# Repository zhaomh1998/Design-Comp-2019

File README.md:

# **Team PI/Stroll Easy**
## This repo is dedicated to all the files created for UCSD 2019 Design Competetion

### Participating Parties:
* < Add Names Here >

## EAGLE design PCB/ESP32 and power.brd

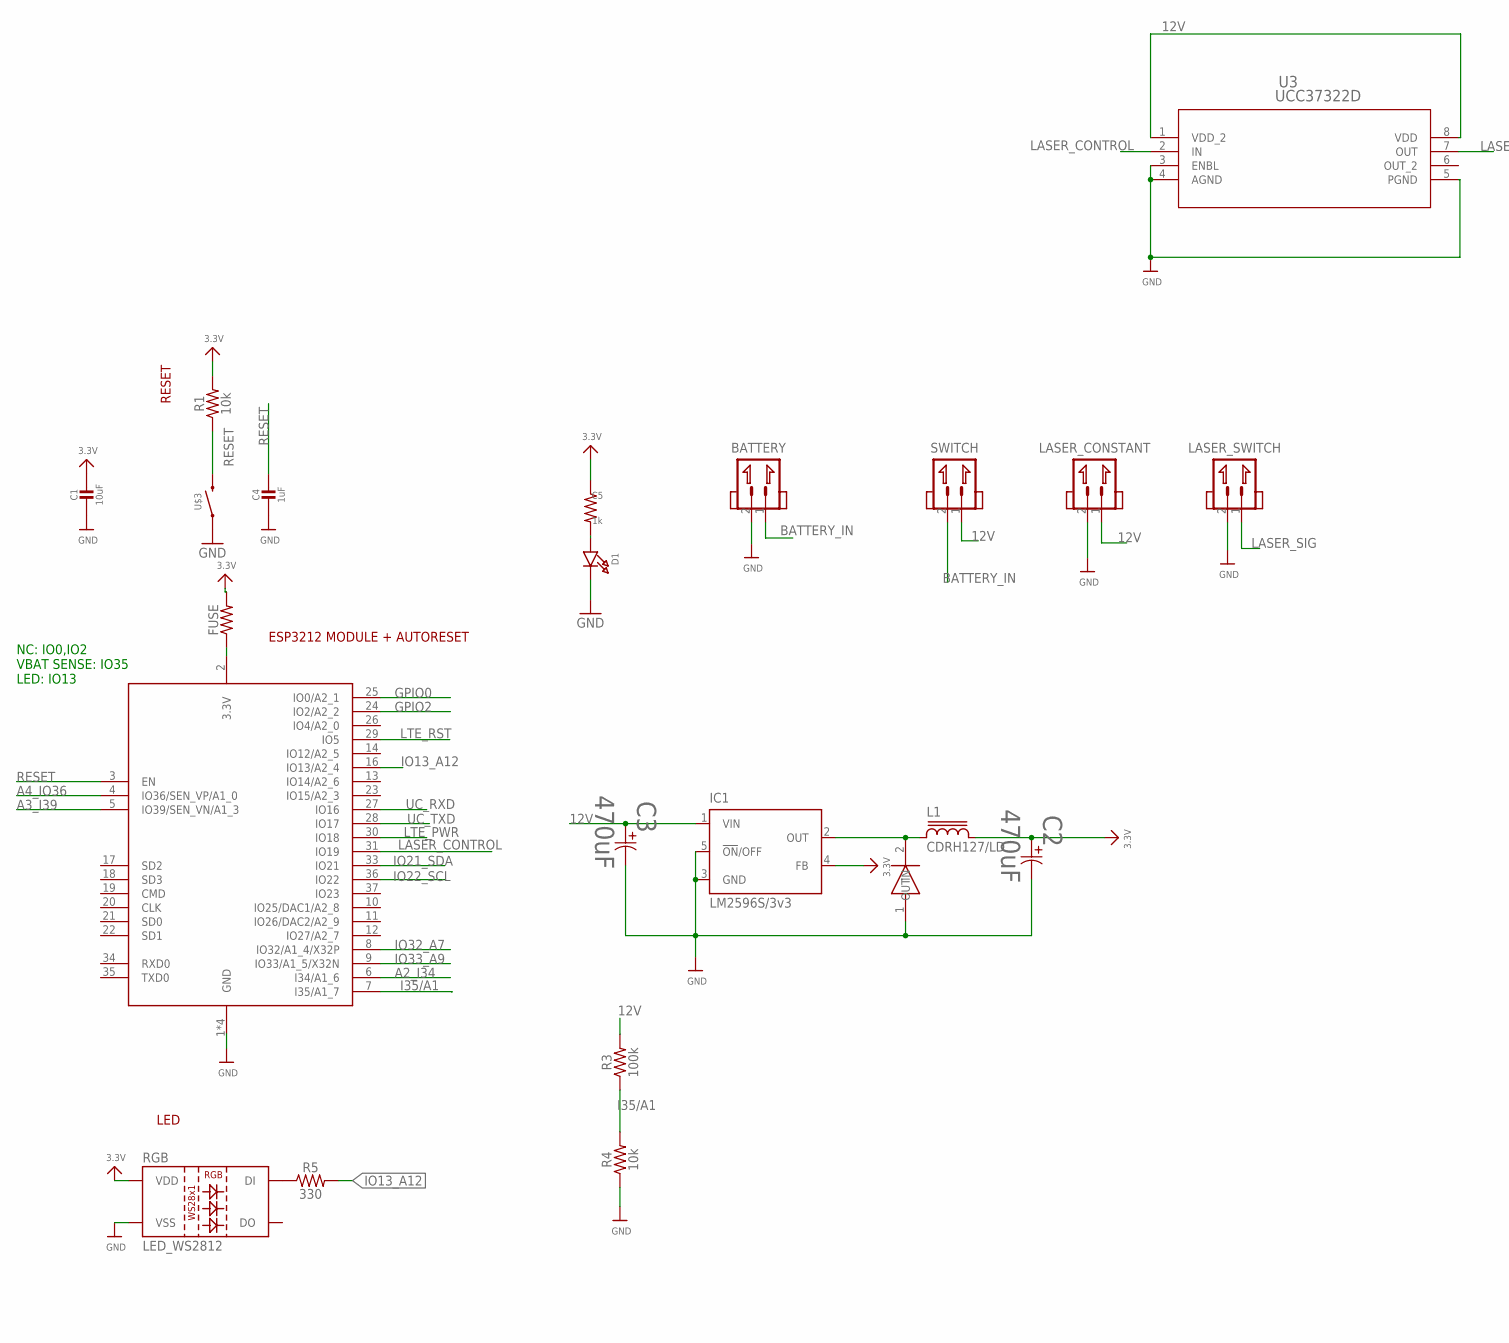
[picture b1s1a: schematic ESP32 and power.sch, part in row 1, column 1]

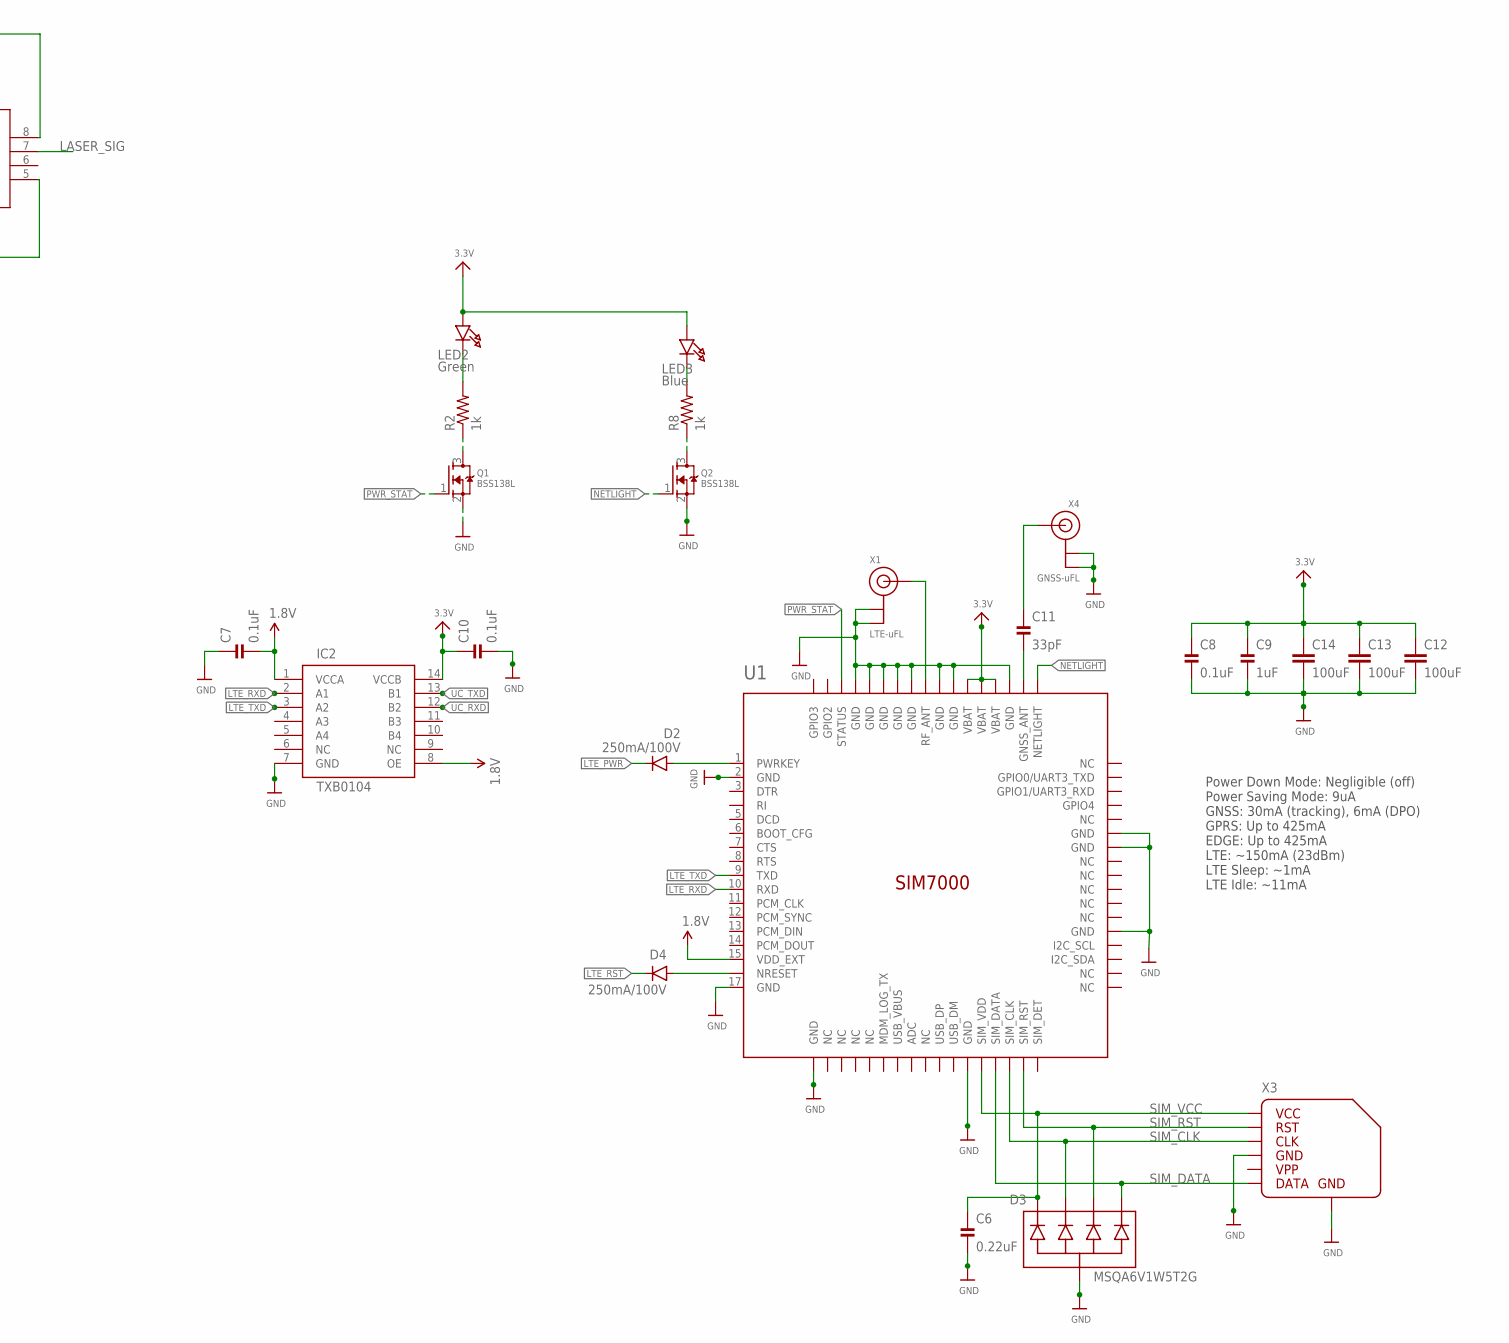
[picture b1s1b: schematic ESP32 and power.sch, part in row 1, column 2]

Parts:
BATTERY: JST_XH_2.54_2P
C1: 10uF; CAP_0603
C2, C3: 470uF; PCAP_8X10-ELECT
C4, C9: 1uF; CAP_0603
C5: 1k; 0603
C6: 0.22uF; CAP_0603
C7, C8, C10: 0.1uF; CAP_0603
C11: 33pF; CAP_0603
C12, C13, C14: 100uF; 1210
D1: LED0603; MICROBUILDER_CHIPLED_0603
D2, D4: 250mA/100V; SOD-323
D3: MSQA6V1W5T2G; SOT-353
FUSE: 1206
IC1: LM2596S/3v3; TO263-5
IC2: TXB0104; TSSOP-14
L1: CDRH127/LD
LASER_CONSTANT: JST_XH_2.54_2P
LASER_SWITCH: JST_XH_2.54_2P
LED2: Green; MICROBUILDER_CHIPLED_0603
LED3: Blue; MICROBUILDER_CHIPLED_0603
Q1, Q2: BSS138L; SOT23-3
R1, R4: 10k; 0603
R2, R8: 1k; 0603
R3: 100k; 0603
R5: 330; 0603
RGB: LED_WS2812; LED-TRICOLOR-5050-IC
SS34: 40V3A; SMA-SS34
SWITCH: JST_XH_2.54_2P
U1: SIM7000
U3: UCC37322D; D8
U$3: PUSHBUTTON; TACTILE_SWITCH_SMD_6.0X3.5MM
X1: LTE-uFL; U.FL
X2: ESP32_WROOM32_SKINNY; WROOM32_SKINNY
X3: MICROSIM_SOCKET
X4: GNSS-uFL; U.FL

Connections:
1.8V: C7.2, IC2.1 (VCCA), IC2.8 (OE), U1.15 (VDD_EXT)
3.3V: C1.1, C2.1, C5.1, C8.1, C9.1, C10.1, C12.1, C13.1, C14.1, FUSE.2, IC1.4 (FB), IC2.14 (VCCB), L1.2, LED2.A, LED3.A, R1.2, RGB.VDD, U1.55 (VBAT), U1.56 (VBAT), U1.57 (VBAT)
12V: C3.1, IC1.1 (VIN), LASER_CONSTANT.1, R3.2, SWITCH.1, U3.1 (VDD_2), U3.8 (VDD)
A2_I34: X2.6 (I34/A1_6)
A3_I39: X2.5 (IO39/SEN_VN/A1_3)
A4_IO36: X2.4 (IO36/SEN_VP/A1_0)
BATTERY_IN: BATTERY.1, SWITCH.2
GND: BATTERY.2, C1.2, C2.2, C3.2, C4.2, C6.2, C7.1, C8.2, C9.2, C10.2, C12.2, C13.2, C14.2, D1.C, D3.2 (COM), IC1.3 (GND), IC1.5 (!ON!/OFF), IC2.7 (GND), LASER_CONSTANT.2, LASER_SWITCH.2, Q1.2 (S), Q2.2 (S), R4.1, RGB.VSS, SS34.1 (IN), U1.2 (GND), U1.17 (GND), U1.18 (GND), U1.29 (GND), U1.39 (GND), U1.45 (GND), U1.46 (GND), U1.54 (GND), U1.58 (GND), U1.59 (GND), U1.61 (GND), U1.62 (GND), U1.63 (GND), U1.64 (GND), U1.65 (GND), U3.3 (ENBL), U3.4 (AGND), U3.5 (PGND), U$3.1, X1.1 (GND), X1.2 (GND), X2.1 (GND), X2.15 (GND), X2.38 (GND), X2.P$1 (GND), X3.C5, X3.GND@1 (GND), X3.GND@2 (GND), X3.GND@3 (GND), X3.GND@4 (GND), X4.1 (GND), X4.2 (GND)
GPIO0: X2.25 (IO0/A2_1)
GPIO2: X2.24 (IO2/A2_2)
I35/A1: R3.1, R4.2, X2.7 (I35/A1_7)
IO13_A12: R5.2, X2.16 (IO13/A2_4)
IO21_SDA: X2.33 (IO21)
IO22_SCL: X2.36 (IO22)
IO32_A7: X2.8 (IO32/A1_4/X32P)
IO33_A9: X2.9 (IO33/A1_5/X32N)
LASER_CONTROL: U3.2 (IN), X2.31 (IO19)
LASER_SIG: LASER_SWITCH.1, U3.7 (OUT)
LTE_PWR: D2.C, X2.30 (IO18)
LTE_RST: D4.C, X2.29 (IO5)
LTE_RXD: IC2.2 (A1), U1.10 (RXD)
LTE_TXD: IC2.3 (A2), U1.9 (TXD)
unnamed: IC1.2 (OUT), L1.1, SS34.2 (OUT)
unnamed: R5.1, RGB.DIN (DI)
unnamed: C5.2, D1.A
unnamed: D2.A, U1.1 (PWRKEY)
unnamed: C11.2, U1.53 (GNSS_ANT)
unnamed: C11.1, X4.3 (SIGNAL)
unnamed: Q1.3 (D), R2.1
unnamed: LED2.C, R2.2
unnamed: LED3.C, R8.2
unnamed: Q2.3 (D), R8.1
unnamed: FUSE.1, X2.2 (3.3V)
NETLIGHT: Q2.1 (G), U1.52 (NETLIGHT)
NRESET: D4.A, U1.16 (NRESET)
PWR_STAT: Q1.1 (G), U1.66 (STATUS)
RESET: C4.1, R1.1, U$3.2, X2.3 (EN)
RF_ANT: U1.60 (RF_ANT), X1.3 (SIGNAL)
SIM_CLK: D3.3 (2), U1.32 (SIM_CLK), X3.C3
SIM_DATA: D3.5 (4), U1.31 (SIM_DATA), X3.C7
SIM_RST: D3.4 (3), U1.33 (SIM_RST), X3.C2
SIM_VCC: C6.1, D3.1, U1.30 (SIM_VDD), X3.C1
UC_RXD: IC2.12 (B2), X2.27 (IO16)
UC_TXD: IC2.13 (B1), X2.28 (IO17)

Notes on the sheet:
RESET
LED
ESP3212 MODULE + AUTORESET
NC: IO0,IO2 VBAT SENSE: IO35 LED: IO13
Power Down Mode: Negligible (off) Power Saving Mode: 9uA GNSS: 30mA (tracking), 6mA (DPO) GPRS: Up to 425mA EDGE: Up to 425mA LTE: ~150mA (23dBm) LTE Sleep: ~1mA LTE Idle: ~11mA

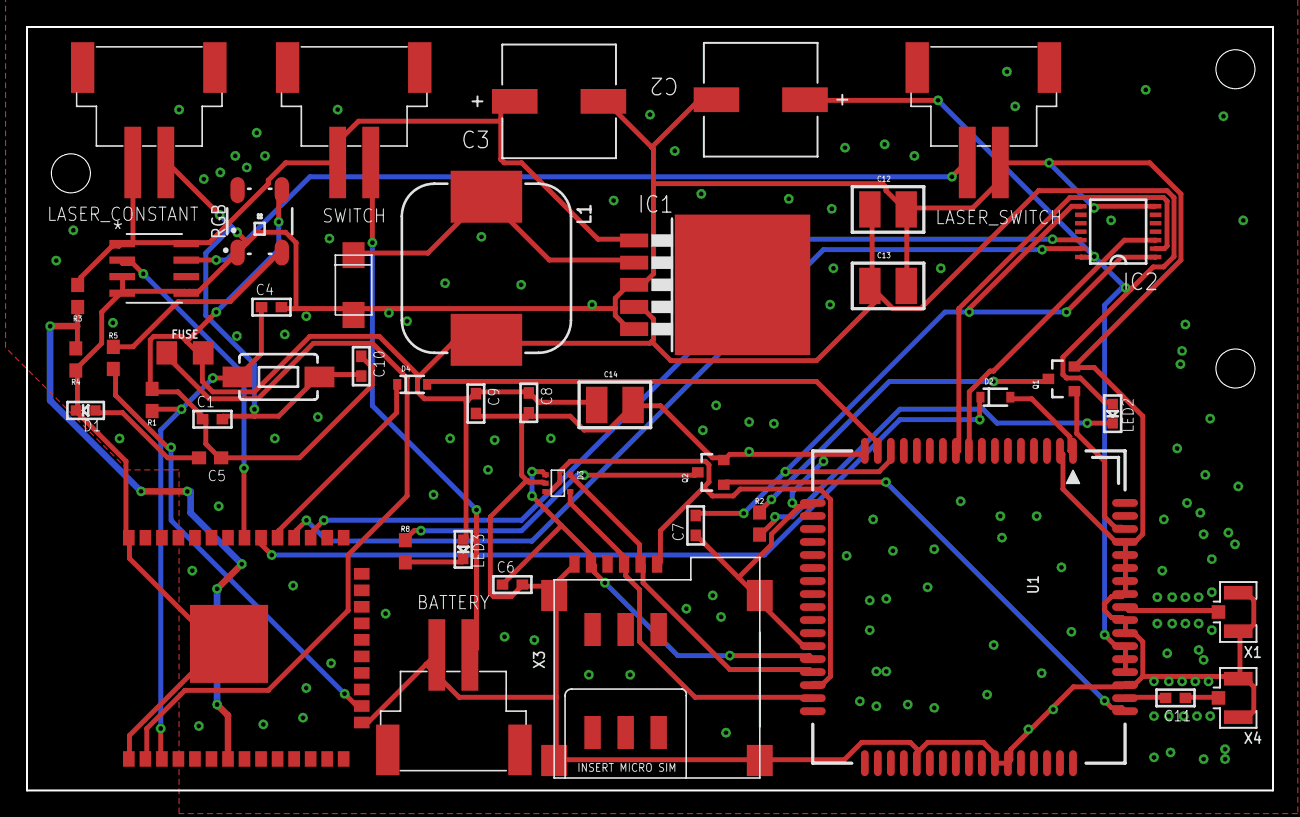
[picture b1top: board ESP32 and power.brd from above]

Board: 2 copper layers, 95.8 x 58.7 mm, 45 parts (0 on the bottom side), 35 nets.

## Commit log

2019-04-30 add LTE test code and mega328p bootloader code
2019-04-30 fix formatting
2019-05-01 created and configured react app
2019-05-01 removed .zip
2019-05-01 backend db, get tests
2019-05-01 Add files via upload
    added gps
2019-05-03 web-app files
2019-05-03 mobile app init
2019-05-08 Firebase auth
2019-05-08 update firebase_auth version, restructure repo
2019-05-09 save log in credential
2019-05-09 auto signin implementation
2019-05-09 DB IO stuff init tests
2019-05-09 map display location from db, walker manage page init
2019-05-13 walker mngr page work, more db implementation
2019-05-13 walker id validation in backend
2019-05-16 added pcb
2019-05-21 ESP final board test
2019-05-22 add SOS necklace
2019-05-24 connect walker mngr with db, add display address
2019-05-29 select patient, map marker
2019-05-29 update map pin, walker manager ui, page routes
2019-05-29 analysis page, update patient list ui; map ui
2019-05-31 add firebase messaging Android
2019-05-31 backend support for sos messaging
2019-05-31 necklace working
2019-05-31 ios init
2019-05-31 update ignore with ios key
2019-06-01 add some assets for app
2019-06-01 working on Android
2019-06-01 ios map working
2019-06-01 more ios configurations
2019-06-01 ios notification working
2019-06-01 add demo login
2019-10-31 Bump eslint-utils from 1.3.1 to 1.4.3 in /web-app
    Bumps [eslint-utils](https://github.com/mysticatea/eslint-utils) from 1.3.1 to 1.4.3.
    - [Release notes](https://github.com/mysticatea/eslint-utils/releases)
    - [Commits](https://github.com/mysticatea/eslint-utils/compare/v1.3.1...v1.4.3)
2019-11-01 Bump lodash from 4.17.11 to 4.17.15 in /web-app
    Bumps [lodash](https://github.com/lodash/lodash) from 4.17.11 to 4.17.15.
    - [Release notes](https://github.com/lodash/lodash/releases)
    - [Commits](https://github.com/lodash/lodash/compare/4.17.11...4.17.15)
2019-11-01 Bump bootstrap from 4.0.0 to 4.3.1 in /web-app
    Bumps [bootstrap](https://github.com/twbs/bootstrap) from 4.0.0 to 4.3.1.
    - [Release notes](https://github.com/twbs/bootstrap/releases)
    - [Commits](https://github.com/twbs/bootstrap/compare/v4.0.0...v4.3.1)
2019-11-01 Bump mixin-deep from 1.3.1 to 1.3.2 in /web-app
    Bumps [mixin-deep](https://github.com/jonschlinkert/mixin-deep) from 1.3.1 to 1.3.2.
    - [Release notes](https://github.com/jonschlinkert/mixin-deep/releases)
    - [Commits](https://github.com/jonschlinkert/mixin-deep/compare/1.3.1...1.3.2)
2019-11-01 Bump lodash.template from 4.4.0 to 4.5.0 in /web-app
    Bumps [lodash.template](https://github.com/lodash/lodash) from 4.4.0 to 4.5.0.
    - [Release notes](https://github.com/lodash/lodash/releases)
    - [Commits](https://github.com/lodash/lodash/compare/4.4.0...4.5.0)
2019-12-28 Bump handlebars from 4.1.2 to 4.5.3 in /web-app
    Bumps [handlebars](https://github.com/wycats/handlebars.js) from 4.1.2 to 4.5.3.
    - [Release notes](https://github.com/wycats/handlebars.js/releases)
    - [Changelog](https://github.com/wycats/handlebars.js/blob/master/release-notes.md)
    - [Commits](https://github.com/wycats/handlebars.js/compare/v4.1.2...v4.5.3)
2020-03-14 Bump acorn from 5.7.3 to 5.7.4 in /web-app
    Bumps [acorn](https://github.com/acornjs/acorn) from 5.7.3 to 5.7.4.
    - [Release notes](https://github.com/acornjs/acorn/releases)
    - [Commits](https://github.com/acornjs/acorn/compare/5.7.3...5.7.4)
2020-06-06 Bump websocket-extensions from 0.1.3 to 0.1.4 in /web-app
    Bumps [websocket-extensions](https://github.com/faye/websocket-extensions-node) from 0.1.3 to 0.1.4.
    - [Release notes](https://github.com/faye/websocket-extensions-node/releases)
    - [Changelog](https://github.com/faye/websocket-extensions-node/blob/master/CHANGELOG.md)
    - [Commits](https://github.com/faye/websocket-extensions-node/compare/0.1.3...0.1.4)
2020-07-17 Bump lodash from 4.17.15 to 4.17.19 in /web-app
    Bumps [lodash](https://github.com/lodash/lodash) from 4.17.15 to 4.17.19.
    - [Release notes](https://github.com/lodash/lodash/releases)
    - [Commits](https://github.com/lodash/lodash/compare/4.17.15...4.17.19)
2020-07-30 Bump elliptic from 6.4.1 to 6.5.3 in /web-app
    Bumps [elliptic](https://github.com/indutny/elliptic) from 6.4.1 to 6.5.3.
    - [Release notes](https://github.com/indutny/elliptic/releases)
    - [Commits](https://github.com/indutny/elliptic/compare/v6.4.1...v6.5.3)
2020-09-08 Bump http-proxy from 1.17.0 to 1.18.1 in /web-app
    Bumps [http-proxy](https://github.com/http-party/node-http-proxy) from 1.17.0 to 1.18.1.
    - [Release notes](https://github.com/http-party/node-http-proxy/releases)
    - [Changelog](https://github.com/http-party/node-http-proxy/blob/master/CHANGELOG.md)
    - [Commits](https://github.com/http-party/node-http-proxy/compare/1.17.0...1.18.1)
2021-03-09 Bump elliptic from 6.5.3 to 6.5.4 in /web-app
    Bumps [elliptic](https://github.com/indutny/elliptic) from 6.5.3 to 6.5.4.
    - [Release notes](https://github.com/indutny/elliptic/releases)
    - [Commits](https://github.com/indutny/elliptic/compare/v6.5.3...v6.5.4)
2021-03-30 Bump y18n from 4.0.0 to 4.0.1 in /web-app
    Bumps [y18n](https://github.com/yargs/y18n) from 4.0.0 to 4.0.1.
    - [Release notes](https://github.com/yargs/y18n/releases)
    - [Changelog](https://github.com/yargs/y18n/blob/master/CHANGELOG.md)
    - [Commits](https://github.com/yargs/y18n/commits)
2021-04-20 Bump ssri from 6.0.1 to 6.0.2 in /web-app
    Bumps [ssri](https://github.com/npm/ssri) from 6.0.1 to 6.0.2.
    - [Release notes](https://github.com/npm/ssri/releases)
    - [Changelog](https://github.com/npm/ssri/blob/v6.0.2/CHANGELOG.md)
    - [Commits](https://github.com/npm/ssri/compare/v6.0.1...v6.0.2)
2021-05-07 Bump handlebars from 4.5.3 to 4.7.7 in /web-app
    Bumps [handlebars](https://github.com/wycats/handlebars.js) from 4.5.3 to 4.7.7.
    - [Release notes](https://github.com/wycats/handlebars.js/releases)
    - [Changelog](https://github.com/handlebars-lang/handlebars.js/blob/master/release-notes.md)
    - [Commits](https://github.com/wycats/handlebars.js/compare/v4.5.3...v4.7.7)
2021-05-07 Bump url-parse from 1.4.7 to 1.5.1 in /web-app
    Bumps [url-parse](https://github.com/unshiftio/url-parse) from 1.4.7 to 1.5.1.
    - [Release notes](https://github.com/unshiftio/url-parse/releases)
    - [Commits](https://github.com/unshiftio/url-parse/compare/1.4.7...1.5.1)
2021-05-08 Bump lodash from 4.17.19 to 4.17.21 in /web-app
    Bumps [lodash](https://github.com/lodash/lodash) from 4.17.19 to 4.17.21.
    - [Release notes](https://github.com/lodash/lodash/releases)
    - [Commits](https://github.com/lodash/lodash/compare/4.17.19...4.17.21)
2021-05-10 Bump hosted-git-info from 2.7.1 to 2.8.9 in /web-app
    Bumps [hosted-git-info](https://github.com/npm/hosted-git-info) from 2.7.1 to 2.8.9.
    - [Release notes](https://github.com/npm/hosted-git-info/releases)
    - [Changelog](https://github.com/npm/hosted-git-info/blob/v2.8.9/CHANGELOG.md)
    - [Commits](https://github.com/npm/hosted-git-info/compare/v2.7.1...v2.8.9)
2021-05-27 Bump dns-packet from 1.3.1 to 1.3.4 in /web-app
    Bumps [dns-packet](https://github.com/mafintosh/dns-packet) from 1.3.1 to 1.3.4.
    - [Release notes](https://github.com/mafintosh/dns-packet/releases)
    - [Changelog](https://github.com/mafintosh/dns-packet/blob/master/CHANGELOG.md)
    - [Commits](https://github.com/mafintosh/dns-packet/compare/v1.3.1...v1.3.4)
2021-06-07 Bump merge-deep from 3.0.2 to 3.0.3 in /web-app
    Bumps [merge-deep](https://github.com/jonschlinkert/merge-deep) from 3.0.2 to 3.0.3.
    - [Release notes](https://github.com/jonschlinkert/merge-deep/releases)
    - [Commits](https://github.com/jonschlinkert/merge-deep/compare/3.0.2...3.0.3)
    ---
    updated-dependencies:
    - dependency-name: merge-deep
2021-06-15 Bump postcss from 7.0.14 to 7.0.36 in /web-app
    Bumps [postcss](https://github.com/postcss/postcss) from 7.0.14 to 7.0.36.
    - [Release notes](https://github.com/postcss/postcss/releases)
    - [Changelog](https://github.com/postcss/postcss/blob/main/CHANGELOG.md)
    - [Commits](https://github.com/postcss/postcss/compare/7.0.14...7.0.36)
    ---
    updated-dependencies:
2021-08-10 Bump path-parse from 1.0.6 to 1.0.7 in /web-app
    Bumps [path-parse](https://github.com/jbgutierrez/path-parse) from 1.0.6 to 1.0.7.
    - [Release notes](https://github.com/jbgutierrez/path-parse/releases)
    - [Commits](https://github.com/jbgutierrez/path-parse/commits/v1.0.7)
    ---
    updated-dependencies:
    - dependency-name: path-parse
2021-09-04 Bump color-string from 1.5.3 to 1.6.0 in /web-app
    Bumps [color-string](https://github.com/Qix-/color-string) from 1.5.3 to 1.6.0.
    - [Release notes](https://github.com/Qix-/color-string/releases)
    - [Changelog](https://github.com/Qix-/color-string/blob/master/CHANGELOG.md)
    - [Commits](https://github.com/Qix-/color-string/commits/1.6.0)
    ---
    updated-dependencies:
2021-09-04 Bump url-parse from 1.4.7 to 1.5.3 in /web-app
    Bumps [url-parse](https://github.com/unshiftio/url-parse) from 1.4.7 to 1.5.3.
    - [Release notes](https://github.com/unshiftio/url-parse/releases)
    - [Commits](https://github.com/unshiftio/url-parse/compare/1.4.7...1.5.3)
    ---
    updated-dependencies:
    - dependency-name: url-parse
2021-09-04 Bump ws from 5.2.2 to 5.2.3 in /web-app
    Bumps [ws](https://github.com/websockets/ws) from 5.2.2 to 5.2.3.
    - [Release notes](https://github.com/websockets/ws/releases)
    - [Commits](https://github.com/websockets/ws/compare/5.2.2...5.2.3)
    ---
    updated-dependencies:
    - dependency-name: ws

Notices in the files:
parts and their libraries:
microbuilder: This work is placed in the public domain, and may be freely used for commercial and non-commercial work with the following conditions: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
inductor-sumida: Copyright (C) 2008, Bob Starr
